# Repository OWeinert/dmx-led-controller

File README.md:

<!-- PROJECT HEADER -->
<div align="center">
  <h1 align="center">Led Matrix Controller</h1>
  
  <p align="center">
    Awesome self rendered animations for common led matrices.
  </p>
</div>

## Getting Started

On your rpi:
1. Install [Rust][Rust-installation-guide]
2. clone repo
3. ```./code/run.sh```
4. done

More tips:
- [Headless raspberry pi setup][Headless-rpi-setup]

## Simulate Display

On your pc:
1. Install [Rust][Rust-installation-guide]
2. clone repo
3. ```./code/run.sh run --simulate```
4. done

## Cross Compile

The detailed [guide][Rust-cross-compile] covers most of the information.
The rpi-led-matrix lib is more difficult to cross compile.
Configure the ```CrossCompileConfig.toml``` to use the right compiler
and also configure ```run.sh``` to use the right target host.

Then run
```./code/run.sh --deploy```.

## Remote Debugging

Configure ```run.sh```.

Then run ```./code/run.sh --gdbserver``` in one terminal
and use Bundled GDB for remote debugging.

## Built With
[![Next][Rust]][Rust-url]

## License
Distributed under the GNU General Public License v3.0. See `LICENSE.txt` for more information.

<!-- MARKDOWN LINKS & IMAGES
Banner: https://torange.biz/photofxnew/207/HD/polygonal-red-metal-texture-led-207754.jpg
-->
[Rust]: https://img.shields.io/badge/rust-000000?style=for-the-badge&logo=rust&logoColor=white
[Rust-url]: https://www.rust-lang.org/
[Headless-rpi-setup]: https://www.tomshardware.com/reviews/raspberry-pi-headless-setup-how-to,6028.html
[Rust-installation-guide]: https://www.rust-lang.org/tools/install
[Rust-cross-compile]: https://github.com/japaric/rust-cross/blob/master/README.md

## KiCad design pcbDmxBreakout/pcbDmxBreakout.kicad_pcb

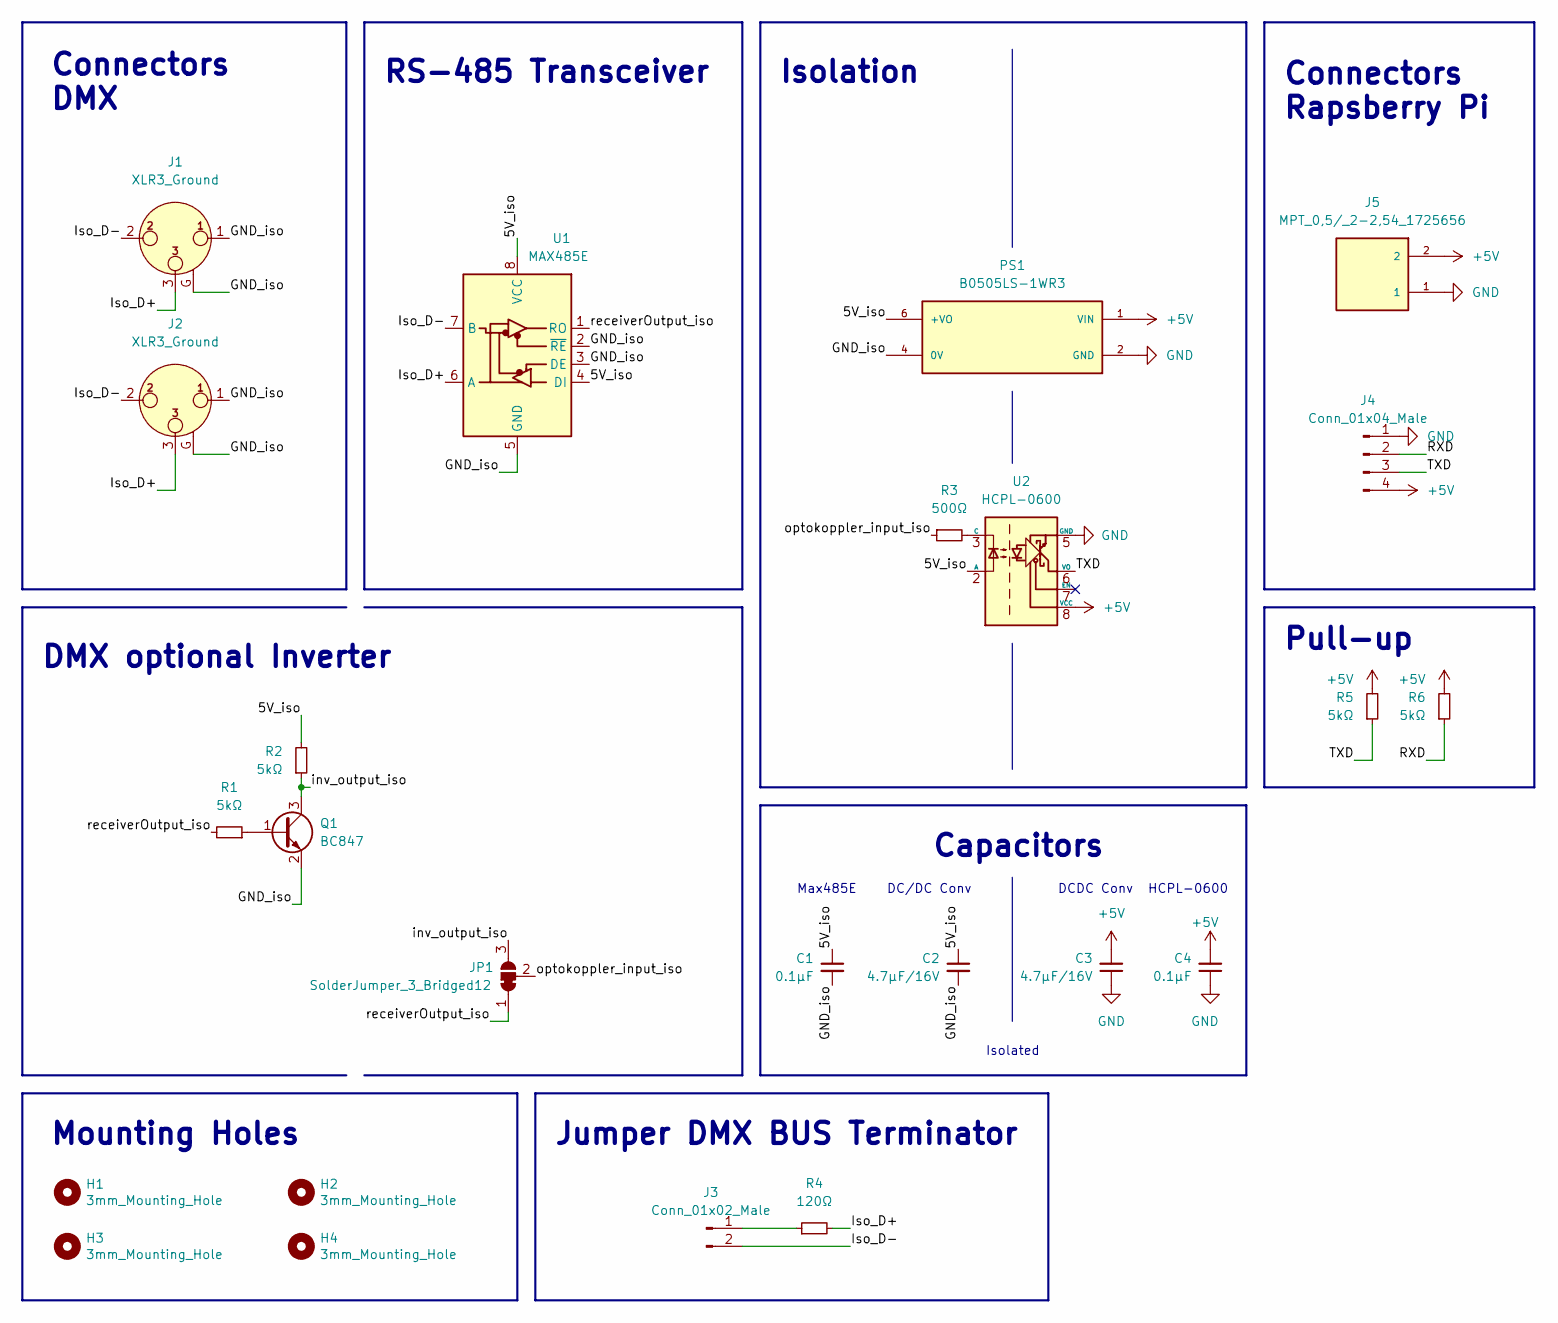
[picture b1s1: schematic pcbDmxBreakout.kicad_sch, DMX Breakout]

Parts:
C1, C4: 0.1µF; C_0805_2012Metric; mouser PartNr 710-885012207045
C2, C3: 4.7µF/16V; C_0805_2012Metric; mouser PartNr 187-CL21A475KQFNNNE
H1, H2, H3, H4: 3mm_Mounting_Hole; MountingHole_3mm
J1: XLR3_Ground; NEUTRIK_NC3MAH; mouser PartNr 568-NC3MAH-LR
J2: XLR3_Ground; NEUTRIK_NC3FAH2; mouser PartNr 568-NC3FAH-2
J3: Conn_01x02_Male; PinHeader_1x02_P2.54mm_Vertical; mouser PartNr 649-67997-100HLF
J4: Conn_01x04_Male; PinHeader_1x04_P2.54mm_Horizontal; mouser PartNr 649-67997-100HLF
J5: MPT_0,5/_2-2,54_1725656; PH_MPT_0,5__2-2,54_1725656; MPN MPT 0,5/ 2-2,54 1725656; mouser PartNr 651-1725656
JP1: SolderJumper_3_Bridged12; SolderJumper-3_P1.3mm_Bridged12_RoundedPad1.0x1.5mm_NumberL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
PS1: B0505LS-1WR3; CONV_B0505LS-1WR3; PARTREV 2019.10.15-A/5; mouser PartNr 919-RFB-0505S
Q1: BC847; SOT-23; mouser PartNr 771-BC847C-QR
R1, R2, R5, R6: 5kΩ; R_0805_2012Metric; mouser PartNr 71-CRCW0805J-5K
R3: 500Ω; R_0805_2012Metric; mouser PartNr 603-RT0805BRD07505RL
R4: 120Ω; R_0805_2012Metric; mouser PartNr 755-SDR10EZPJ121
U1: MAX485E; SO-8_3.9x4.9mm_P1.27mm; mouser PartNr 700-MAX485CSA
U2: HCPL-0600; SO-8_3.9x4.9mm_P1.27mm; mouser PartNr 630-HCPL-0600-560E

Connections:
+5V: C3.2, C4.2, J4.4, J5.2, PS1.1 (VIN), R5.2, R6.2, U2.8 (VCC)
/5V_iso: C1.1, C2.1, PS1.6 (+VO), R2.2, U1.4 (DI), U1.8 (VCC), U2.2 (A)
/GND_iso: C1.2, C2.2, J1.1, J1.G, J2.1, J2.G, PS1.4 (0V), Q1.2 (E), U1.2 (~RE), U1.3 (DE), U1.5 (GND)
/Iso_D+: J1.3, J2.3, R4.2, U1.6 (A)
/Iso_D-: J1.2, J2.2, J3.2, U1.7 (B)
/RXD: J4.2, R6.1
/TXD: J4.3, R5.1, U2.6 (VO)
/inv_output_iso: JP1.3 (B), Q1.3 (C), R2.1
/optokoppler_input_iso: JP1.2 (C), R3.1
/receiverOutput_iso: JP1.1 (A), R1.2, U1.1 (RO)
GND: C3.1, C4.1, J4.1, J5.1, PS1.2 (GND), U2.5 (GND)
unnamed: J3.1, R4.1
unnamed: Q1.1 (B), R1.1
unnamed: R3.2, U2.3 (C)

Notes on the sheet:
RS-485 Transceiver
Jumper DMX BUS Terminator
Connectors DMX
Mounting Holes
Capacitors
Connectors Rapsberry Pi
Isolation
DCDC Conv
Pull-up
Max485E
DMX optional Inverter
DC/DC Conv
HCPL-0600
Isolated

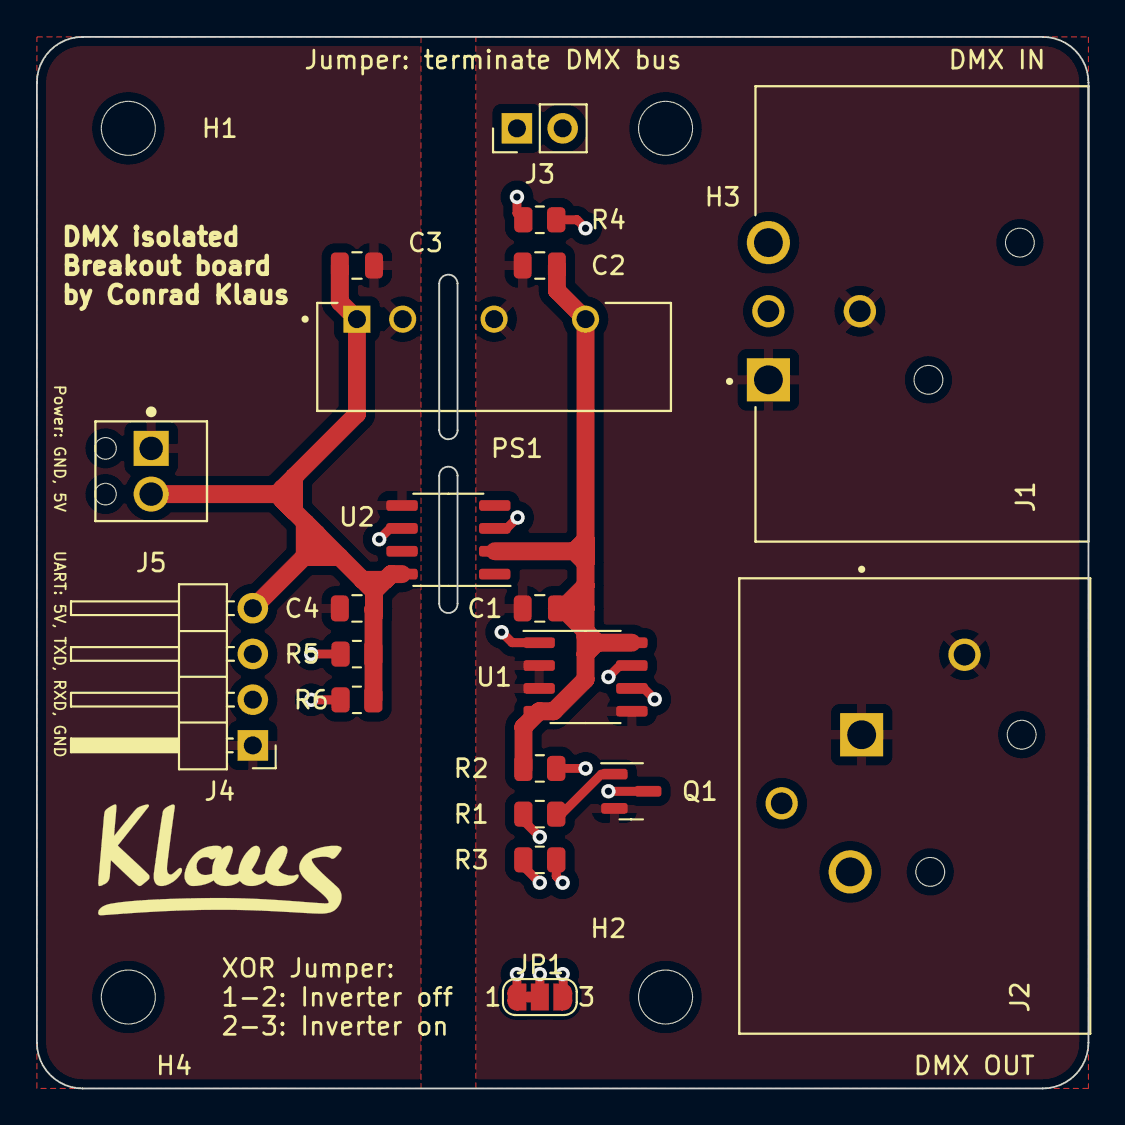
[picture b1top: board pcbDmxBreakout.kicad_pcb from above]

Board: 4 copper layers, 58.4 x 58.4 mm, 24 parts (0 on the bottom side), 14 nets.

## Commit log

2022-09-09 init rust project
2022-09-13 add simple led matrix line example
2022-09-13 improve run configuration and add simple graphics
2022-09-15 add display simulator
2022-09-29 add simple wireframe render
2022-10-03 render triangle faces, include obj files
2022-10-13 add movable camera
2022-10-13 move project code to sub folder
2022-10-13 add thesis template
2022-10-13 simplify and customize template
2022-10-16 add expose
2022-10-16 add TU Berlin Template
2022-10-16 add Antrittsvortrag
2022-10-16 correct uDMX PID
2022-10-16 add uDMX commandline from https://github.com/mirdej/udmx
2022-10-26 update Expose
2022-11-30 add bachelor thesis template
2022-12-01 customize bachelor thesis
2023-02-05 add PCB DMX Breakout Schematics
2023-02-10 add Breakout board PCB
2023-02-21 add case
2023-03-08 add simple c code
2023-03-09 add sigrok-cli as c lib
2023-03-10 simplify sigrok for dmx analyzer
2023-03-12 simplify sigrok, mostly everything unnecessary
2023-03-12 add simple c to rust callback
2023-03-12 add sigrok decoder callback to rust code
2023-03-18 receive live decoder stream
    remove everything unnecessary from sigrok-cli
2023-03-19 refactor structure of libLogicAnalyzer
2023-03-20 visualize dmx data on display
2023-03-20 read sigrok logic analyzer data optionally from a file
2023-03-21 add Abstract, Chapter: Protokolle Lichttechnik
2023-03-23 add dmx decode state machine
2023-03-30 add render engine with dmx overlay.
    dmx channels 1 - 3 controls rgb channels
2023-03-30 add mockup for channel 1 timing analyzer
2023-04-24 improve text
2023-04-24 add dmx analyzer viewpages for hardware and simulation add thesis
2023-04-24 add more citations
2023-08-10 Remove unused files
2023-08-11 Seperate lib and bin into own crates
2023-08-11 Add relative_path dependency
2023-08-11 move python folder to display crate for testing
2023-08-11 Move python folder back to start location
2023-08-11 Rename io module to core
2023-08-11 Rename func startup() to setup()
2023-08-11 Update dlcl targets
2023-08-11 Implement loading of interop_test.py
2023-08-11 Add comments
2023-08-11 Add pyo3 features
2023-08-11 Update targets
2023-08-11 Remove fn init_python
2023-08-11 Add module ext_module
2023-08-11 Add gitignore to dlcl, fixed gitignore of display
2023-08-11 Change README
2023-08-11 Changed .gitignore files
2023-08-11 moved draw module to draw.rs
2023-08-11 Add ext_module.rs
2023-08-11 fix gitignore not working
2023-08-11 fix typ in draw.rs
2023-08-11 Implement draw module
2023-08-11 Remove invalid Cargo.toml from settings
2023-08-11 Add once_cell dependency
2023-08-11 Implement functionality to exisiting functions
2023-08-11 Change use of module dlcl::interop::python
2023-08-12 Update dependency versions
2023-08-12 Fully implement draw_pixel function, fix draw_framebuffer error
2023-08-12 add comment line
2023-08-12 add test animation for framebuffer
2023-08-12 Fix frame buffer swapped x/y, Add draw_circle, Add circles to display
2023-08-12 draw_line and draw_circle now use PrimitiveStyle
2023-08-12 Cleanup
2023-08-17 add py_venv folder to .gitignore
2023-08-17 add iter_tools dependency
2023-08-17 split draw.rs into multiple files in own module, add layer module
2023-08-17 rename ext_module to pymodule
2023-08-17 fully implement and fix layers and framebuffer
2023-08-17 add test draw for layers
2023-08-17 improve draw_framebuffer function
2023-08-17 add layout for interop::c module, add CRgb888 struct, add c_draw_pixel_direct() function
2023-09-05 remove c interop, moved python interop module remove DlclDrawTarget
2023-09-16 remove py_interop
2023-09-16 add animation module
2023-09-16 add rpc module
2023-09-16 add LayerManager, rework Layers
2023-09-16 add dlcl rpc protocol
2023-09-16 fix layer errors, remove unused and unnecessary code
2023-09-16 Add DlclNet solution structure, remove interop_test.py
2023-09-16 add .gitignore
2023-09-16 move proto to code parent folder
2023-09-16 add reference to .proto file, add grpc nuget packages
2023-09-17 change Class1.cs to DlclClient.cs
2023-09-23 Change layer_manager from type &'a LayerManager to Mutex<LayerManager>, remove lifetime identifier of DlclDrawService, implement push_animations
2023-09-23 Add draw_frame_layer() method
2023-09-23 implement RpcOp::DrawFullLayer in process_rpc_ops() method
2023-09-23 Add from_frames() method
2023-09-23 Add new() method
2023-09-23 Fix typo, add ERROR_UNDEFINED Status
2023-09-23 Add error handling for push_animations() method, add comments
2023-09-23 Add comments, remove redundant comments
2023-10-01 implemented gRpc server in simulated display
2023-10-01 Implemented Client and Client Hosted Service, Added needed Models
2023-10-01 fixed gitignore
2023-10-05 Add GetAnimationQueue, DrawFullLayer, DrawOnLayer and DrawDirect to rpc service
2023-10-05 Added method scaffolds for new rpc service methods to DlclDrawService
2023-10-05 Added Dto mapping extension methods
2023-10-05 Added AddFrame and AddFrames methods
2023-10-05 Added method scaffolds for new rpc service methods to DlclClient
2023-10-07 implemented draw_on_layer
2023-10-07 Split Frame into IFrame interface and SingleFrame and TimedFrame structs, renamed occurences of "DTO" to "Dto"
2023-10-07 Added DrawLayerRequest
2023-10-07 Implemented missing Rpc Service methods
